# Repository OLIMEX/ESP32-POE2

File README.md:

# ESP32-POE2
Power Over Ethernet Internet of Things POE IoT board with Espressif ESP32 WiFi, Bluetooth and wired 100Mbit Ethehernet with 25W power delivery

https://www.olimex.com/Products/IoT/ESP32/ESP32-POE2/open-source-hardware

## Licensee
* Hardware is released under CERN Open Hardware Licence Version 2 - Strongly Reciprocal
* Box design is released under CC BY 4.0 License
* Software is released under GPL V3 Licensee
* Documentation is released under CC BY-SA 4.0

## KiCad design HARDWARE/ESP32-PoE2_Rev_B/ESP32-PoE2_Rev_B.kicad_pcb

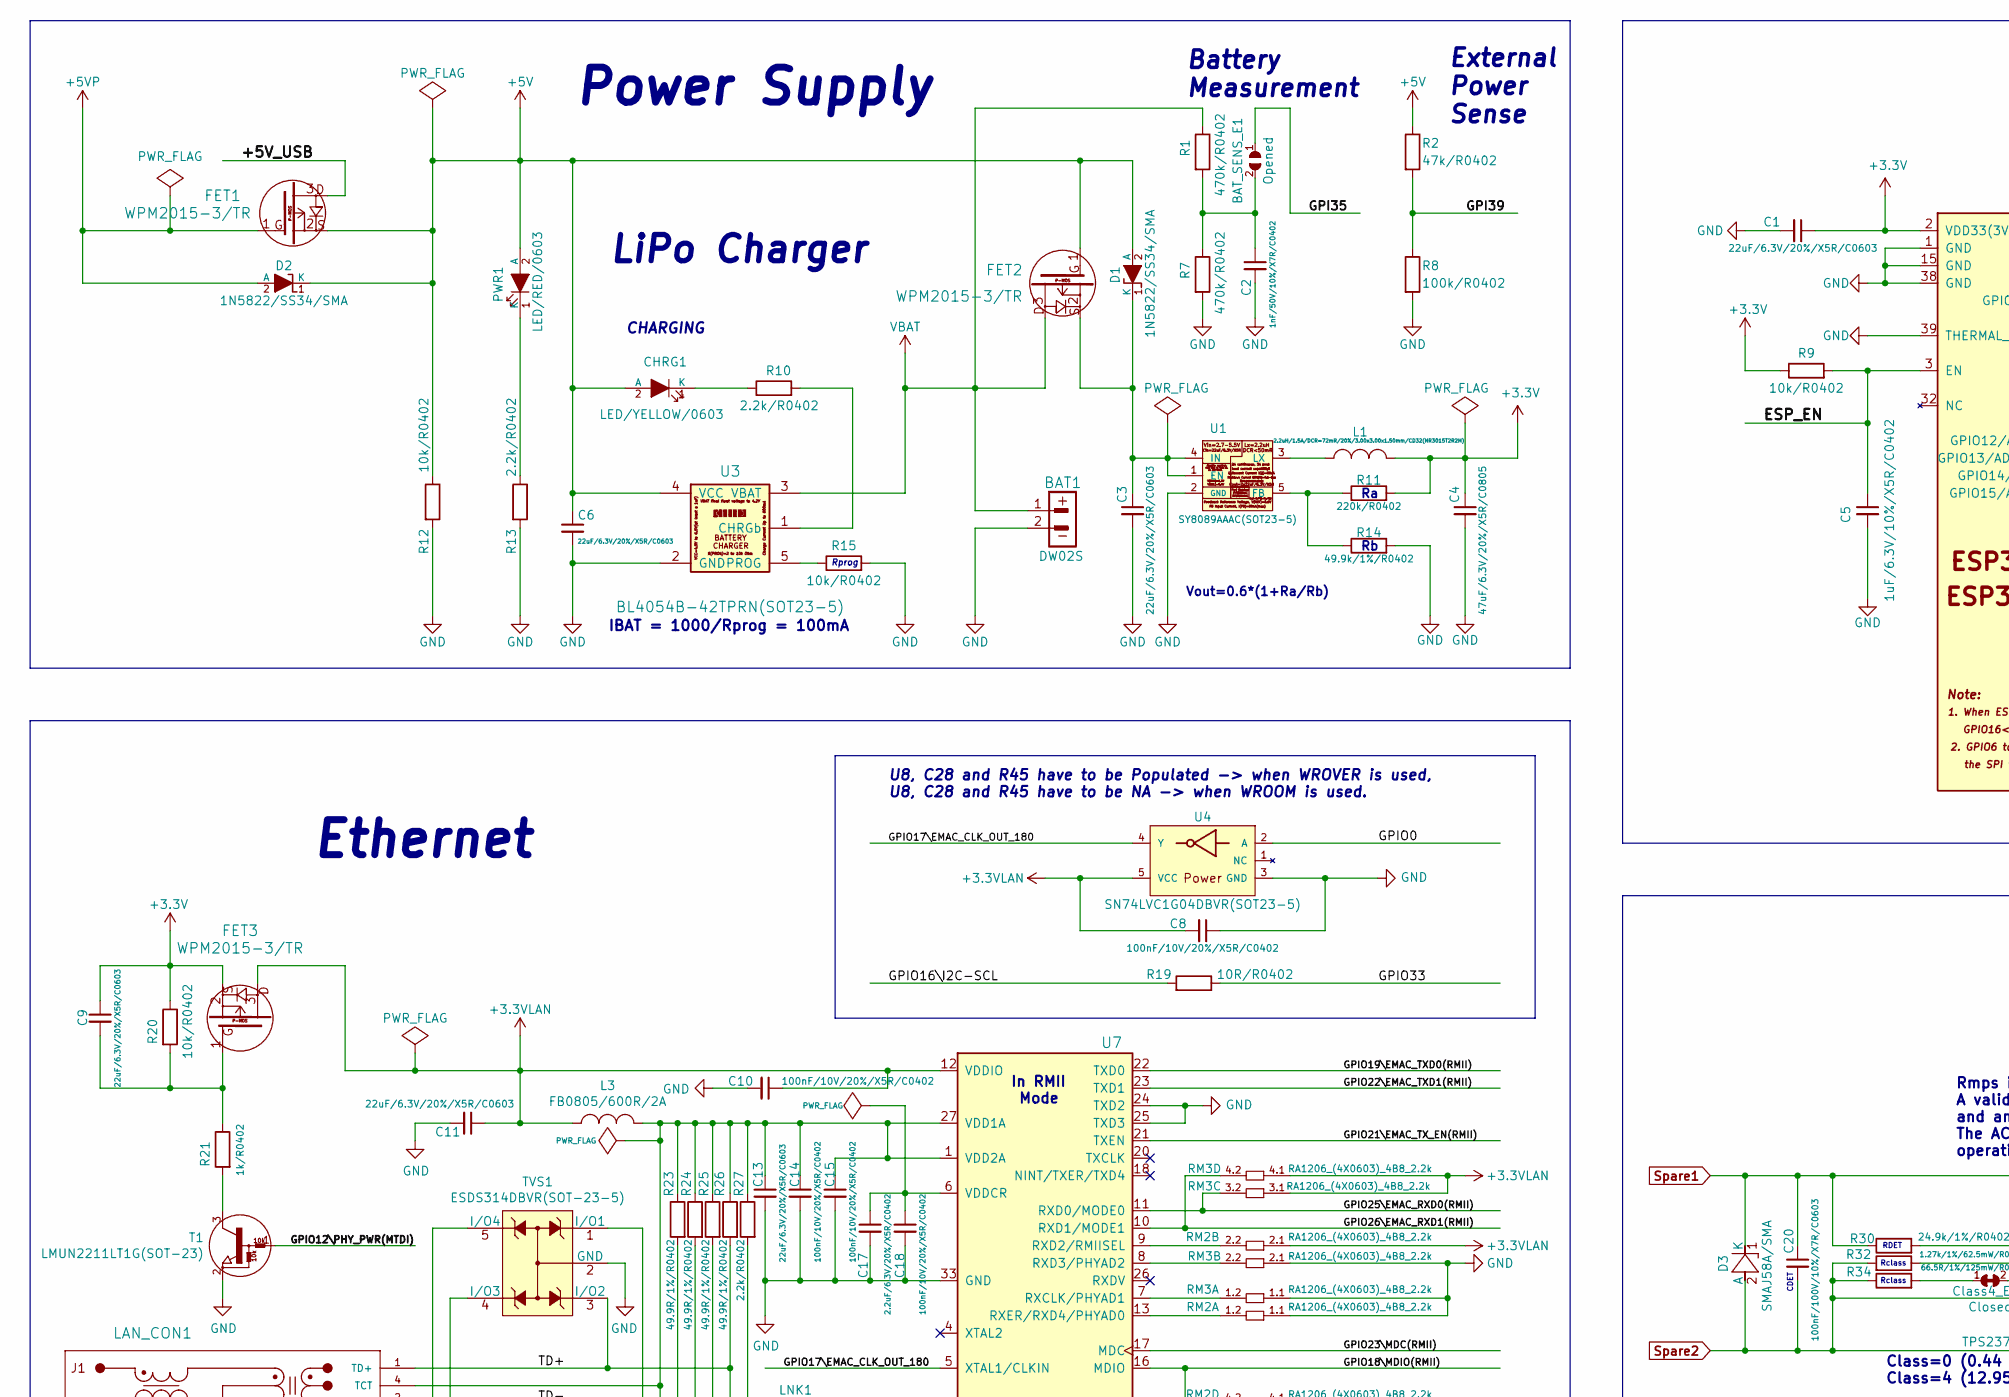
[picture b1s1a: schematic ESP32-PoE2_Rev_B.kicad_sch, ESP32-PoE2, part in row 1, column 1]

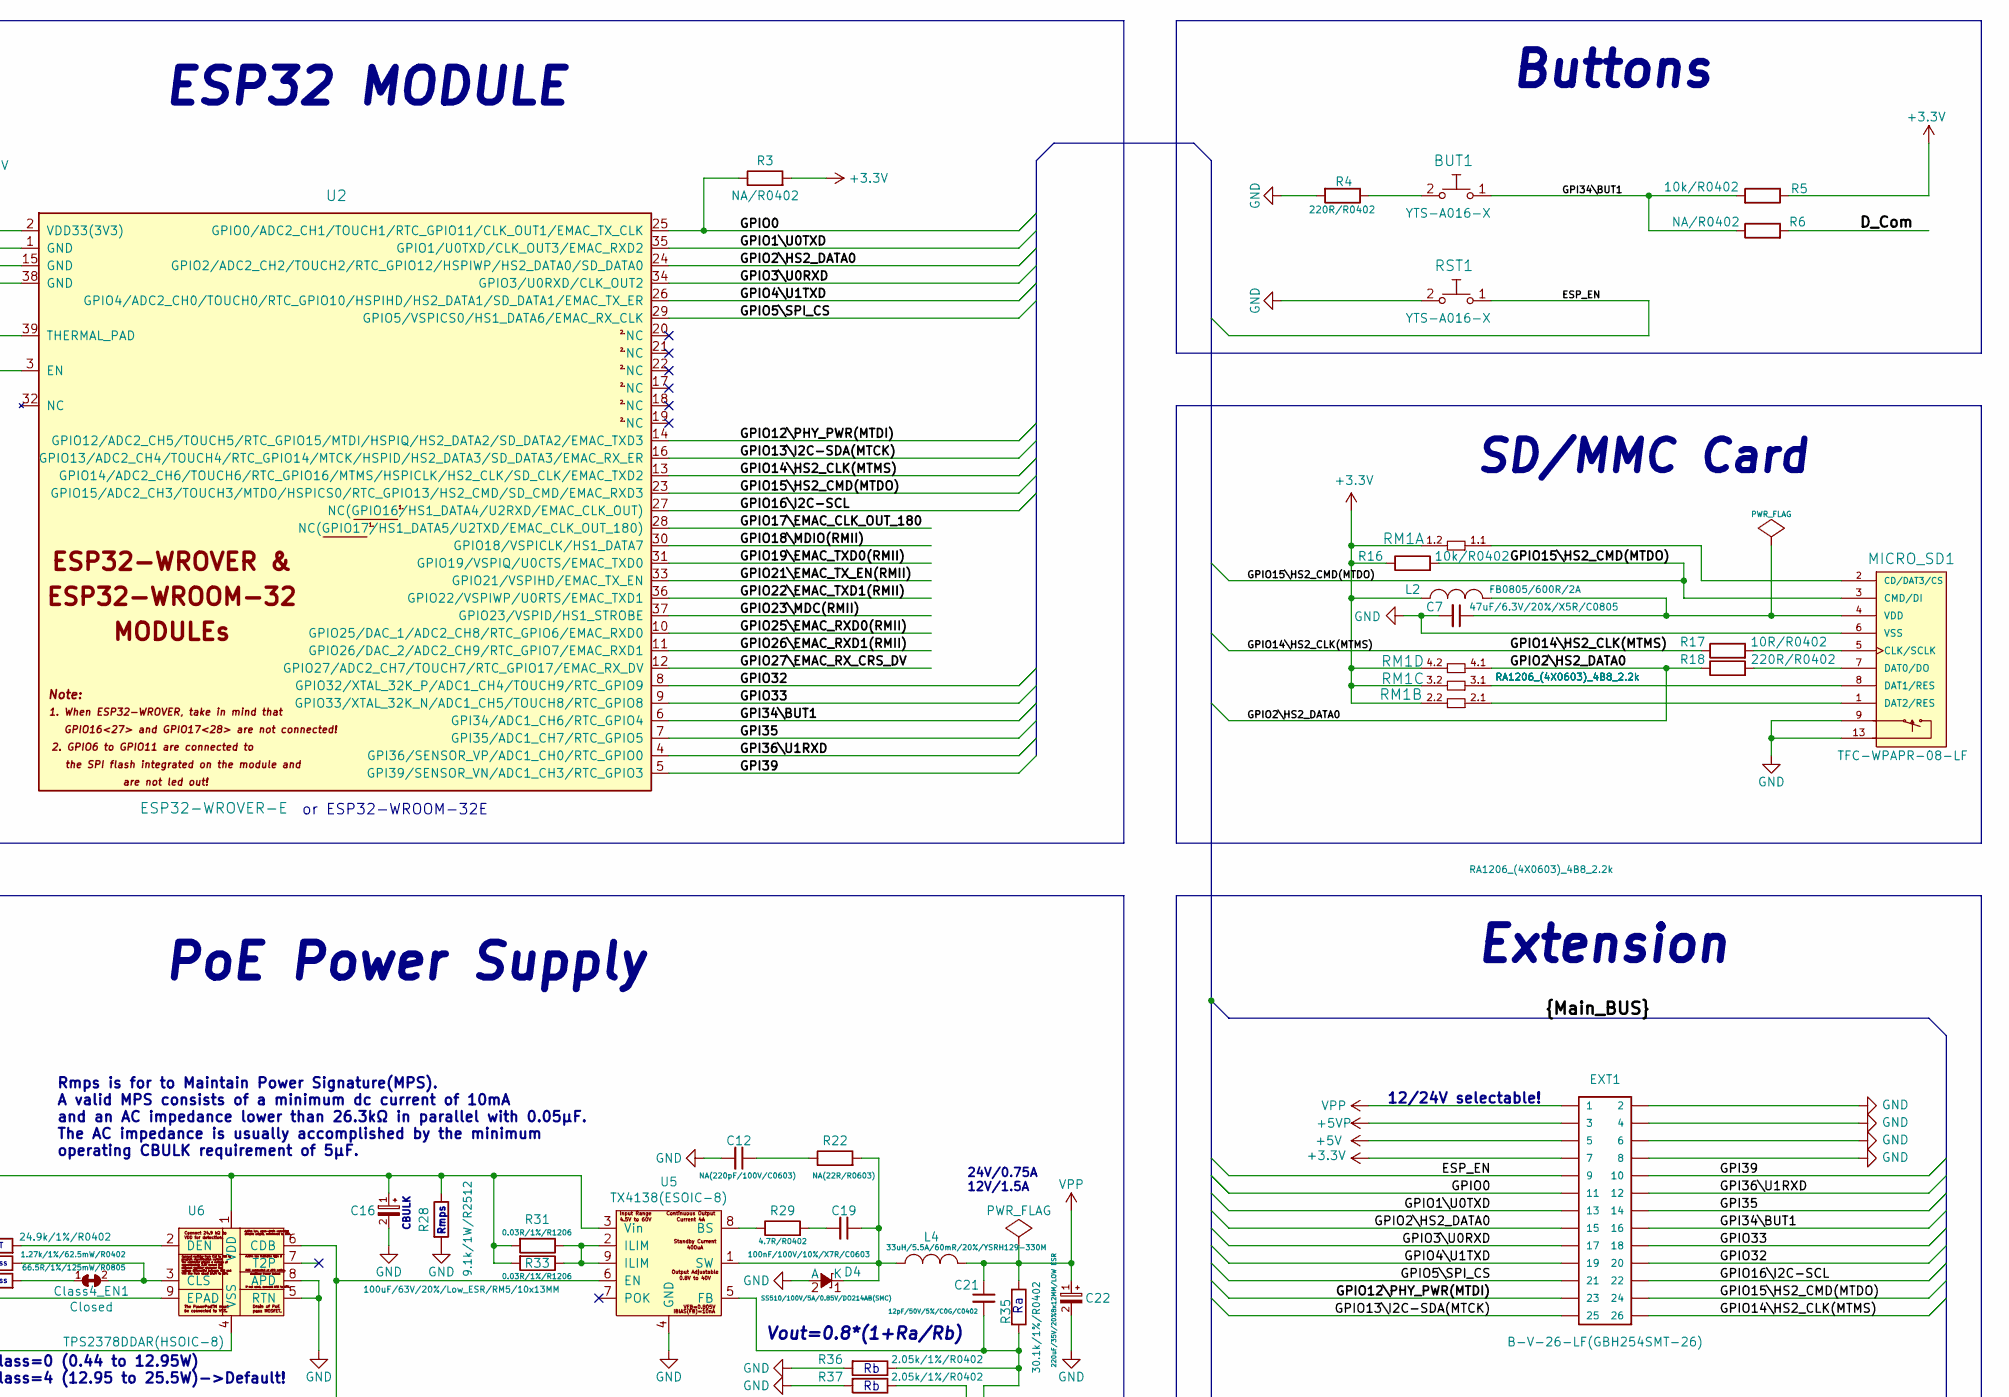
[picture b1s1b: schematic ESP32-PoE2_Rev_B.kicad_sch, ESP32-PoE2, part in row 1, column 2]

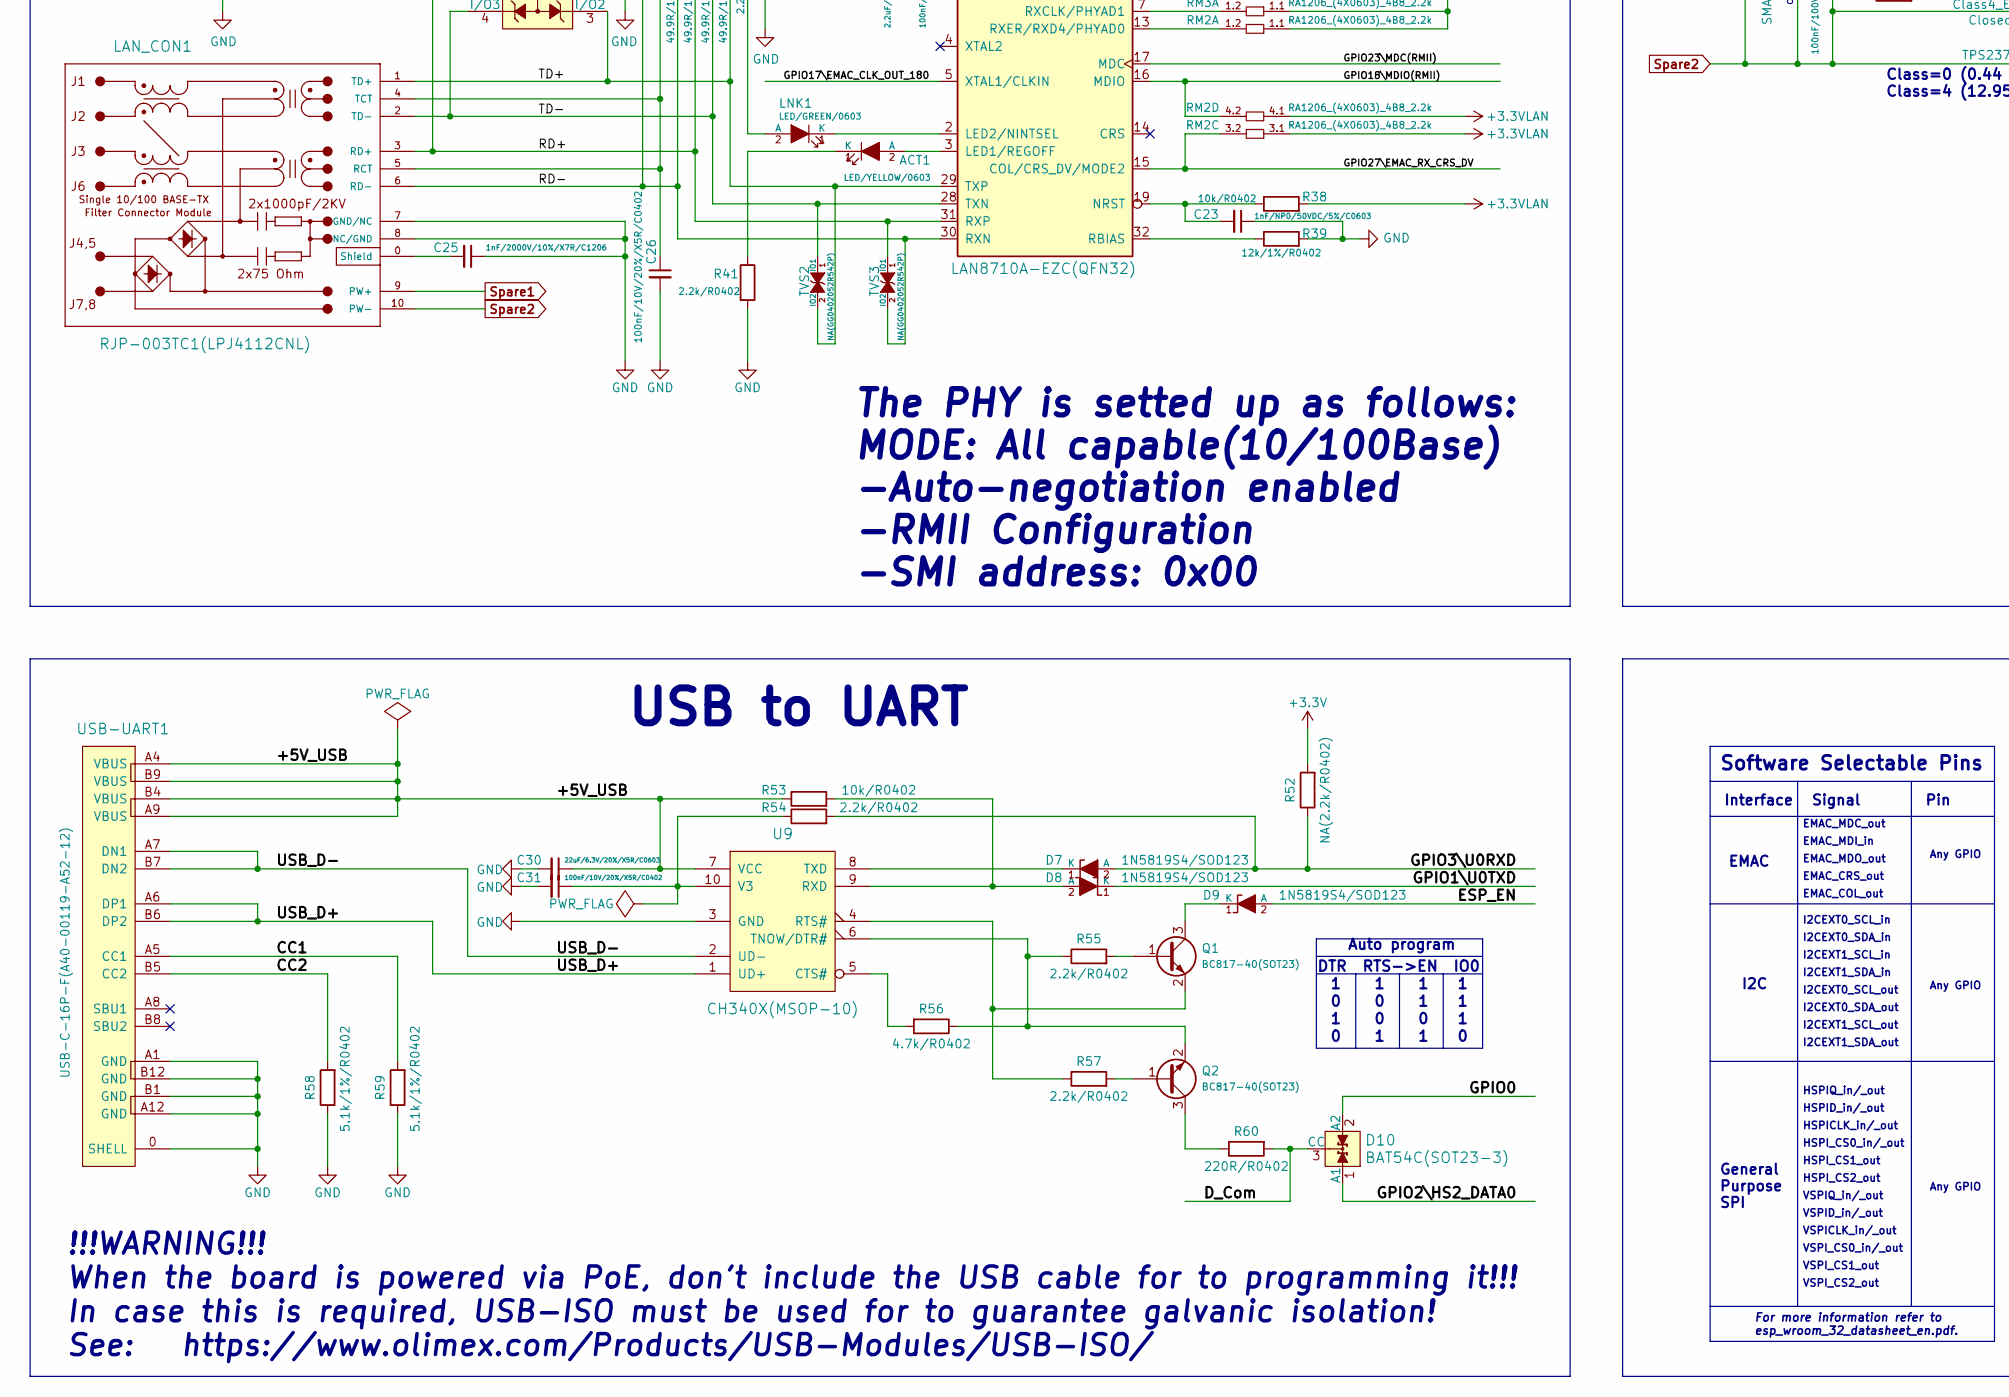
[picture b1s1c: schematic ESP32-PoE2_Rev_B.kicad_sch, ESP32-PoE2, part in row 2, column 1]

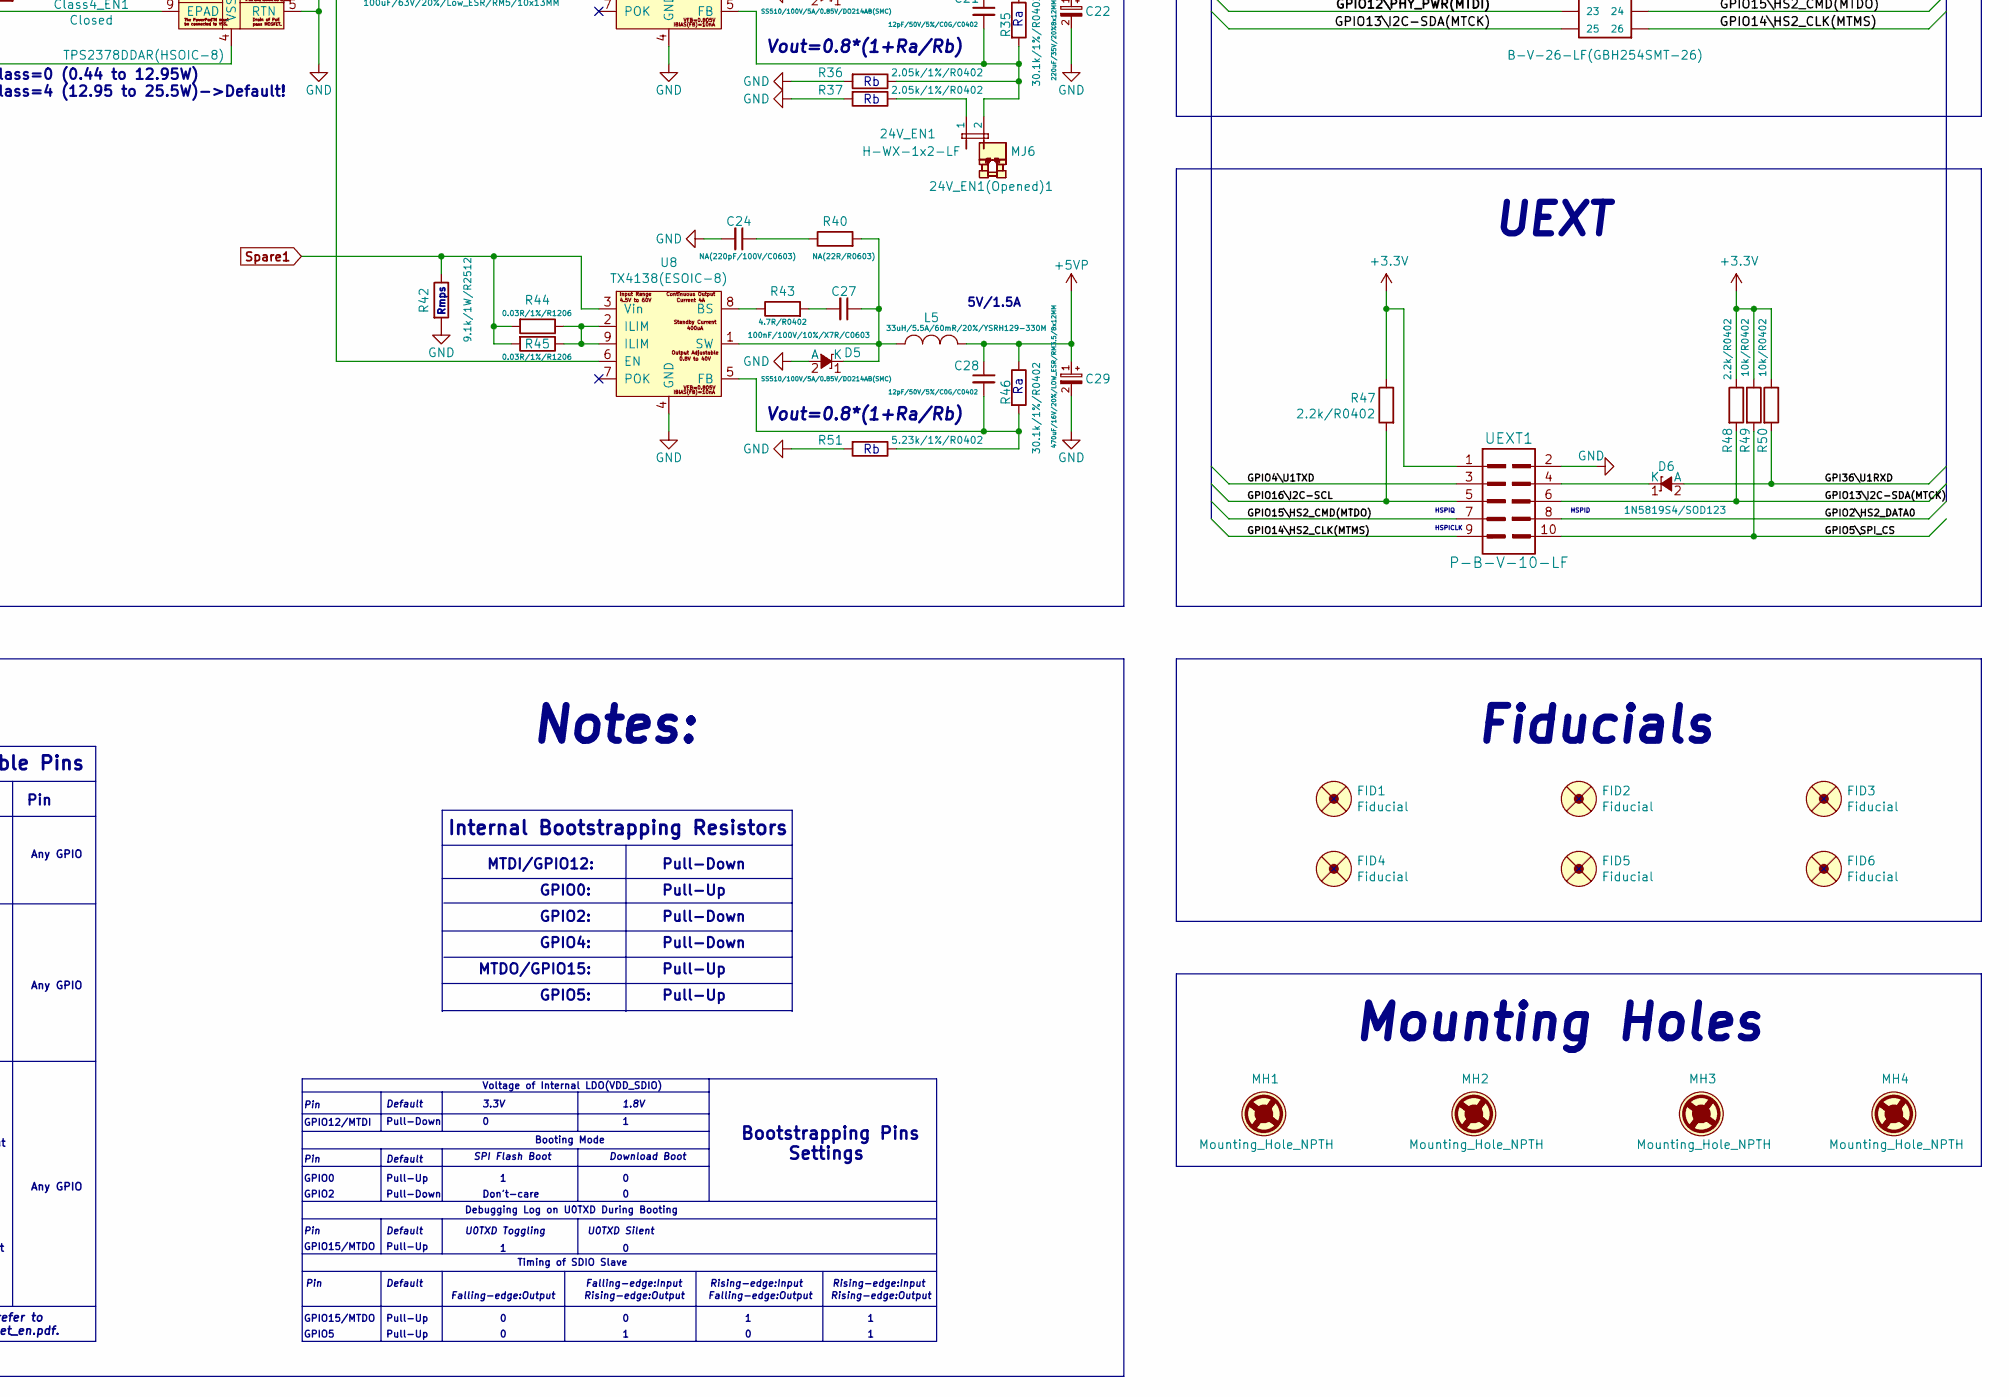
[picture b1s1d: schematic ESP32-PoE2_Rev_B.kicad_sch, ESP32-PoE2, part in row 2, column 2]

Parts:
24V_EN1: H-WX-1x2-LF; HN1x2(SMD)_H-WX-1x2-LF
24V_EN1(Opened)1: MJ6
ACT1: LED/YELLOW/0603; LED_0603_KA
BAT1: DW02S; LIPO_BAT_VERTICAL_DW02S
BAT_SENS_E1: Opened; SJ
BUT1: YTS-A016-X
C1, C3, C6, C9, C11, C13, C30: 22uF/6.3V/20%/X5R/C0603; C_0603_5MIL_DWS
C2: 1nF/50V/10%/X7R/C0402; C_0402_5MIL_DWS
C4, C7: 47uF/6.3V/20%/X5R/C0805; C_0805_5MIL_DWS
C5: 1uF/6.3V/10%/X5R/C0402; C_0402_5MIL_DWS
C8, C10, C14, C15, C18, C26, C31: 100nF/10V/20%/X5R/C0402; C_0402_5MIL_DWS
C12, C24: NA(220pF/100V/C0603); C_0603_5MIL_DWS
C16: 100uF/63V/20%/Low_ESR/RM5/10x13MM; CPOL-RM5mm_10.0x16.0mm_PTH
C17: 2.2uF/6.3V/20%/X5R/C0402; C_0402_5MIL_DWS
C19, C20, C27: 100nF/100V/10%/X7R/C0603; C_0603_5MIL_DWS
C21, C28: 12pF/50V/5%/C0G/C0402; C_0402_5MIL_DWS
C22: 220uF/35V/20%8x12MM/LOW ESR; CPOL-RM3.5mm_8.0x11.5mm_PTH
C23: 1nF/NP0/50VDC/5%/C0603; C_0603_5MIL_DWS
C25: 1nF/2000V/10%/X7R/C1206; C_1206_5MIL_DWS_ISO
C29: 470uF/16V/20%/LOW_ESR/RM3.5/8x12MM; CPOL-RM3.5mm_8.0x11.5mm_PTH
CHRG1: LED/YELLOW/0603; LED_0603_KA
Class4_EN1: Closed; SJ_Closed
D1, D2: 1N5822/SS34/SMA; SMA-KA
D3: SMAJ58A/SMA; SMA-KA
D4, D5: SS510/100V/5A/0.85V/DO214AB(SMC); DO214AB(SMC)_1(K)-2(A)
D6, D7, D8, D9: 1N5819S4/SOD123; SOD-123_1C-2A_KA
D10: BAT54C(SOT23-3); SOT23-3
EXT1: B-V-26-LF(GBH254SMT-26); GBH-254-SMT-26
FET1, FET2, FET3: WPM2015-3/TR; SOT23
FID1, FID2, FID3: Fiducial; Fiducial1x3_Paste
FID4, FID5, FID6: Fiducial; Fiducial1x3
L1: 2.2uH/1.5A/DCR=72mR/20%/3.00x3.00x1.50mm/CD32(NR3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; CD32
L2, L3: FB0805/600R/2A; L_0805_5MIL_DWS
L4, L5: 33uH/5.5A/60mR/20%/YSRH129-330M; HSMRH129_12.0x12.5x9.5(max)
LAN_CON1: RJP-003TC1(LPJ4112CNL)
LNK1: LED/GREEN/0603; LED_0603_KA
MH1, MH2, MH3, MH4: Mounting_Hole_NPTH; Mounting_Hole_Drill-3.3mm_Clerance-7mm
MICRO_SD1: TFC-WPAPR-08-LF; TFC-WPAPR-08
PWR1: LED/RED/0603; LED_0603_KA
Q1, Q2: BC817-40(SOT23); SOT23
R1, R7: 470k/R0402; R_0402_5MIL_DWS
R2: 47k/R0402; R_0402_5MIL_DWS
R3, R6: NA/R0402; R_0402_5MIL_DWS
R4, R18, R60: 220R/R0402; R_0402_5MIL_DWS
R5, R9, R12, R15, R16, R20, R38, R49, R50, R53: 10k/R0402; R_0402_5MIL_DWS
R8: 100k/R0402; R_0402_5MIL_DWS
R10, R13, R27, R41, R47, R48, R54, R55, R57: 2.2k/R0402; R_0402_5MIL_DWS
R11: 220k/R0402; R_0402_5MIL_DWS
R14: 49.9k/1%/R0402; R_0402_5MIL_DWS
R17, R19: 10R/R0402; R_0402_5MIL_DWS
R21: 1k/R0402; R_0402_5MIL_DWS
R22, R40: NA(22R/R0603); R_0603_5MIL_DWS
R23, R24, R25, R26: 49.9R/1%/R0402; R_0402_5MIL_DWS
R28, R42: 9.1k/1W/R2512; R_2512_MM_DWS
R29, R43: 4.7R/R0402; R_0402_5MIL_DWS
R30: 24.9k/1%/R0402; R_0402_5MIL_DWS
R31, R33, R44, R45: 0.03R/1%/R1206; R_1206_5MIL_DWS
R32: 1.27k/1%/62.5mW/R0402; R_0402_5MIL_DWS
R34: 66.5R/1%/125mW/R0805; R_0805_5MIL_DWS
R35, R46: 30.1k/1%/R0402; R_0402_5MIL_DWS
R36, R37: 2.05k/1%/R0402; R_0402_5MIL_DWS
R39: 12k/1%/R0402; R_0402_5MIL_DWS
R51: 5.23k/1%/R0402; R_0402_5MIL_DWS
R52: NA(2.2k/R0402); R_0402_5MIL_DWS
R56: 4.7k/R0402; R_0402_5MIL_DWS
R58, R59: 5.1k/1%/R0402; R_0402_5MIL_DWS
RM1, RM2, RM3: RA1206_(4X0603)_4B8_2.2k; R_MATRIX_4
RST1: YTS-A016-X
T1: LMUN2211LT1G(SOT-23); SOT23
TVS1: ESDS314DBVR(SOT-23-5); SOT-23-5
TVS2, TVS3: NA(GG0402052R542P); D_0402_5MIL_DWS
U1: SY8089AAAC(SOT23-5); SOT-23-5
U2: ESP32-WROVER-E; ESP32-WROVER(WROOM)-UNIVERSAL_MODULE
U3: BL4054B-42TPRN(SOT23-5); SOT-23-5
U4: SN74LVC1G04DBVR(SOT23-5); SOT-23-5
U5, U8: TX4138(ESOIC-8); ESOIC-8
U6: TPS2378DDAR(HSOIC-8); ESOIC-8
U7: LAN8710A-EZC(QFN32); QFN32_EP(33)_5.00x5.00x0.90mm_Pitch_0.50mm
U9: CH340X(MSOP-10); MSOP-10_Pitch-0.5mm_3.00x3.00x1.00mm
UEXT1: P-B-V-10-LF; GBH-254-SMT-10
USB-UART1: USB-C-16P-F(A40-00119-A52-12); USB2.0_TYPE-C(A40-00119-A52-12)_Paste

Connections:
+3.3V: C1.1, C4.1, C9.1, EXT1.7, FET3.2, L1.2, L2.1, R3.2, R5.1, R9.1, R11.2, R16.1, R20.1, R47.1, R48.1, R49.1, R50.1, R52.2, RM1.1.2, RM1.2.2, RM1.3.2, RM1.4.2, U2.2 (VDD33(3V3)), UEXT1.1
+3.3VLAN: C8.2, C10.1, C11.1, FET3.3, L3.1, R38.2, RM2.2.1, RM2.3.1, RM2.4.1, RM3.3.1, RM3.4.1, U4.5 (VCC), U7.12 (VDDIO)
+5V: C6.1, CHRG1.2 (A), D1.2 (A), D2.1 (K), EXT1.5, FET1.2, FET2.1, PWR1.2 (A), R2.1, R12.1, U3.4 (VCC)
+5VP: C28.1, C29.1 (+), D2.2 (A), EXT1.3, FET1.1, L5.2, R46.1
/+5V_USB: C30.1, FET1.3, R53.1, U9.7 (VCC), USB-UART1.A4 (VBUS), USB-UART1.A9 (VBUS), USB-UART1.B4 (VBUS), USB-UART1.B9 (VBUS)
/CC1: R59.2, USB-UART1.A5 (CC1)
/CC2: R58.2, USB-UART1.B5 (CC2)
/D_Com: D10.3 (CC), R6.2, R60.2
/ESP_EN: C5.1, D9.2 (A), EXT1.9, R9.2, RST1.1, U2.3 (EN)
/GPI34\BUT1: BUT1.1, EXT1.16, R5.2, R6.1, U2.6 (GPI34/ADC1_CH6/RTC_GPIO4)
/GPI35: BAT_SENS_E1.1, EXT1.14, U2.7 (GPI35/ADC1_CH7/RTC_GPIO5)
/GPI36\U1RXD: D6.2 (A), EXT1.12, R50.2, U2.4 (GPI36/SENSOR_VP/ADC1_CH0/RTC_GPIO0)
/GPI39: EXT1.10, R2.2, R8.1, U2.5 (GPI39/SENSOR_VN/ADC1_CH3/RTC_GPIO3)
/GPIO0: D10.2 (A2), EXT1.11, R3.1, U2.25 (GPIO0/ADC2_CH1/TOUCH1/RTC_GPIO11/CLK_OU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), U4.2 (A)
/GPIO1\U0TXD: D8.1 (K), EXT1.13, U2.35 (GPIO1/U0TXD/CLK_OUT3/EMAC_RXD2)
/GPIO2\HS2_DATA0: D10.1 (A1), EXT1.15, R18.1, RM1.4.1, U2.24 (GPIO2/ADC2_CH2/TOUCH2/RTC_GPIO12/HSPIWP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), UEXT1.8
/GPIO3\U0RXD: D7.2 (A), EXT1.17, R52.1, R54.2, U2.34 (GPIO3/U0RXD/CLK_OUT2)
/GPIO4\U1TXD: EXT1.19, U2.26 (GPIO4/ADC2_CH0/TOUCH0/RTC_GPIO10/HSPIHD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), UEXT1.3
/GPIO5\SPI_CS: EXT1.21, R49.2, U2.29 (GPIO5/VSPICS0/HS1_DATA6/EMAC_RX_CLK), UEXT1.10
/GPIO12\PHY_PWR(MTDI): EXT1.23, T1.1 (B), U2.14 (GPIO12/ADC2_CH5/TOUCH5/RTC_GPIO15/MTDI/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)
/GPIO13\I2C-SDA(MTCK): EXT1.25, R48.2, U2.16 (GPIO13/ADC2_CH4/TOUCH4/RTC_GPIO14/MTCK/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), UEXT1.6
/GPIO14\HS2_CLK(MTMS): EXT1.26, R17.1, U2.13 (GPIO14/ADC2_CH6/TOUCH6/RTC_GPIO16/MTMS/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), UEXT1.9
/GPIO15\HS2_CMD(MTDO): EXT1.24, MICRO_SD1.3 (CMD/DI), R16.2, U2.23 (GPIO15/ADC2_CH3/TOUCH3/MTDO/HSPICS0/RTC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), UEXT1.7
/GPIO16\I2C-SCL: EXT1.22, R19.2, R47.2, U2.27 (NC(GPIO16/HS1_DATA4/U2RXD/EMAC_CLK_OUT)), UEXT1.5
/GPIO17\EMAC_CLK_OUT_180: U2.28 (NC(GPIO17/HS1_DATA5/U2TXD/EMAC_CLK_OUT_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), U4.4 (Y), U7.5 (XTAL1/CLKIN)
/GPIO18\MDIO(RMII): RM2.4.2, U2.30 (GPIO18/VSPICLK/HS1_DATA7), U7.16 (MDIO)
/GPIO19\EMAC_TXD0(RMII): U2.31 (GPIO19/VSPIQ/U0CTS/EMAC_TXD0), U7.22 (TXD0)
/GPIO21\EMAC_TX_EN(RMII): U2.33 (GPIO21/VSPIHD/EMAC_TX_EN), U7.21 (TXEN)
/GPIO22\EMAC_TXD1(RMII): U2.36 (GPIO22/VSPIWP/U0RTS/EMAC_TXD1), U7.23 (TXD1)
/GPIO23\MDC(RMII): U2.37 (GPIO23/VSPID/HS1_STROBE), U7.17 (MDC)
/GPIO25\EMAC_RXD0(RMII): RM3.3.2, U2.10 (GPIO25/DAC_1/ADC2_CH8/RTC_GPIO6/EMAC_RX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), U7.11 (RXD0/MODE0)
/GPIO26\EMAC_RXD1(RMII): RM3.4.2, U2.11 (GPIO26/DAC_2/ADC2_CH9/RTC_GPIO7/EMAC_RX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), U7.10 (RXD1/MODE1)
/GPIO27\EMAC_RX_CRS_DV: RM2.3.2, U2.12 (GPIO27/ADC2_CH7/TOUCH7/RTC_GPIO17/EMAC_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), U7.15 (COL/CRS_DV/MODE2)
/GPIO32: EXT1.20, U2.8 (GPIO32/XTAL_32K_P/ADC1_CH4/TOUCH9/RTC_G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)
/GPIO33: EXT1.18, R19.1, U2.9 (GPIO33/XTAL_32K_N/ADC1_CH5/TOUCH8/RTC_G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)
/RD+: LAN_CON1.3 (RD+), R24.2, TVS1.5 (I/O4), TVS3.1 (IO1), U7.31 (RXP)
/RD-: LAN_CON1.6 (RD-), R23.2, TVS1.1 (I/O1), TVS3.2 (IO2), U7.30 (RXN)
/TD+: LAN_CON1.1 (TD+), R26.2, TVS1.3 (I/O2), TVS2.2 (IO2), U7.29 (TXP)
/TD-: LAN_CON1.2 (TD-), R25.2, TVS1.4 (I/O3), TVS2.1 (IO1), U7.28 (TXN)
/USB_D+: U9.1 (UD+), USB-UART1.A6 (DP1), USB-UART1.B6 (DP2)
/USB_D-: U9.2 (UD-), USB-UART1.A7 (DN1), USB-UART1.B7 (DN2)
GND: BAT1.2, C1.2, C2.2, C3.2, C4.2, C5.2, C6.2, C7.2, C8.1, C10.2, C11.2, C12.2, C13.2, C14.2, C15.2, C16.2 (-), C17.2, C18.2, C22.2 (-), C23.1, C24.2, C25.1, C26.2, C29.2 (-), C30.2, C31.2, D4.2 (A), D5.2 (A), EXT1.2, EXT1.4, EXT1.6, EXT1.8, LAN_CON1.7 (GND/NC), LAN_CON1.8 (NC/GND), MICRO_SD1.6 (VSS), MICRO_SD1.9, MICRO_SD1.10, MICRO_SD1.11, MICRO_SD1.12, MICRO_SD1.13, R4.2, R7.2, R8.2, R12.2, R13.2, R14.2, R15.2, R28.2, R36.2, R37.2, R39.2, R41.2, R42.2, R51.2, R58.1, R59.1, RM2.1.1, RM3.1.1, RM3.2.1, RST1.2, T1.2 (E), TVS1.2 (GND), U1.2 (GND), U2.1 (GND), U2.15 (GND), U2.38 (GND), U2.39 (THERMAL_PAD), U3.2 (GND), U4.3 (GND), U5.4 (GND), U6.5 (RTN), U6.8 (APD), U7.24 (TXD2), U7.25 (TXD3), U7.33 (GND), U8.4 (GND), U9.3 (GND), UEXT1.2, USB-UART1.0 (SHELL), USB-UART1.A1 (GND), USB-UART1.A12 (GND), USB-UART1.B1 (GND), USB-UART1.B12 (GND)
unnamed: 24V_EN1.1, R37.1
unnamed: ACT1.2 (A), U7.3 (LED1/REGOFF)
unnamed: ACT1.1 (K), R41.1
unnamed: BAT_SENS_E1.2, C2.1, R1.2, R7.1
unnamed: BUT1.2, R4.1
unnamed: C9.2, FET3.1, R20.2, R21.1
unnamed: C12.1, R22.1
unnamed: C19.2, R29.2
unnamed: C24.1, R40.1
unnamed: C27.2, R43.2
unnamed: CHRG1.1 (K), R10.1
unnamed: Class4_EN1.1, R34.2
unnamed: C3.1, D1.1 (K), FET2.2, U1.1 (EN), U1.4 (IN)
unnamed: C19.1, D4.1 (K), L4.1, R22.2, U5.1 (SW)
unnamed: C27.1, D5.1 (K), L5.1, R40.2, U8.1 (SW)
unnamed: D6.1 (K), UEXT1.4
unnamed: D7.1 (K), U9.8 (TXD)
unnamed: D8.2 (A), R53.2, U9.9 (RXD)
unnamed: D9.1 (K), Q1.3 (C)
unnamed: C13.1, C14.1, C15.1, C26.1, L3.2, LAN_CON1.4 (TCT), LAN_CON1.5 (RCT), R23.1, R24.1, R25.1, R26.1, R27.1, U7.1 (VDD2A), U7.27 (VDD1A)
unnamed: C25.2, LAN_CON1.0 (Shield)
unnamed: LNK1.2 (A), R27.2
unnamed: LNK1.1 (K), U7.2 (LED2/NINTSEL)
unnamed: MICRO_SD1.2 (CD/DAT3/CS), RM1.1.1
unnamed: MICRO_SD1.5 (CLK/SCLK), R17.2
unnamed: MICRO_SD1.7 (DAT0/DO), R18.2
unnamed: MICRO_SD1.8 (DAT1/RES), RM1.3.1
unnamed: MICRO_SD1.1 (DAT2/RES), RM1.2.1
unnamed: C7.1, L2.2, MICRO_SD1.4 (VDD)
unnamed: PWR1.1 (K), R13.1
unnamed: Q1.1 (B), R55.2
unnamed: Q1.2 (E), R57.1, U9.4 (RTS#)
unnamed: Q2.1 (B), R57.2
unnamed: Q2.3 (C), R60.1
unnamed: Q2.2 (E), R55.1, R56.1, U9.6 (TNOW/DTR#)
unnamed: R31.1, R33.1, U5.2 (ILIM), U5.9 (ILIM)
unnamed: R44.1, R45.1, U8.2 (ILIM), U8.9 (ILIM)
unnamed: R21.2, T1.3 (C)
unnamed: R11.1, R14.1, U1.5 (FB)
unnamed: L1.1, U1.3 (LX)
unnamed: R10.2, U3.1 (CHRGb)
unnamed: R15.1, U3.5 (PROG)
unnamed: R29.1, U5.8 (BS)
unnamed: U5.6 (EN), U6.6 (CDB), U8.6 (EN)
unnamed: 24V_EN1.2, C21.2, R35.2, R36.1, U5.5 (FB)
unnamed: Class4_EN1.2, R32.1, U6.3 (CLS)
unnamed: R30.2, U6.2 (DEN)
unnamed: C23.2, R38.1, U7.19 (NRST)
unnamed: R39.1, U7.32 (RBIAS)
unnamed: RM3.1.2, U7.7 (RXCLK/PHYAD1)
unnamed: RM2.2.2, U7.9 (RXD2/RMIISEL)
unnamed: RM3.2.2, U7.8 (RXD3/PHYAD2)
unnamed: RM2.1.2, U7.13 (RXER/RXD4/PHYAD0)
unnamed: C17.1, C18.1, U7.6 (VDDCR)
unnamed: R43.1, U8.8 (BS)
unnamed: C28.2, R46.2, R51.1, U8.5 (FB)
unnamed: R56.2, U9.5 (CTS#)
unnamed: C31.1, R54.1, U9.10 (V3)
Spare1: C16.1 (+), C20.1, D3.1 (K), LAN_CON1.9 (PW+), R28.1, R30.1, R31.2, R33.2, R42.1, R44.2, R45.2, U5.3 (Vin), U6.1 (VDD), U8.3 (Vin)
Spare2: C20.2, D3.2 (A), LAN_CON1.10 (PW-), R32.2, R34.1, U6.4 (VSS), U6.9 (EPAD)
VBAT: BAT1.1, FET2.3, R1.1, U3.3 (VBAT)
VPP: C21.1, C22.1 (+), EXT1.1, L4.2, R35.1

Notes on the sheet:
VSPI_CS0_in/_out
U0TXD Silent
CHARGING
Software Selectable Pins
Buttons
Voltage of Internal LDO(VDD_SDIO)
GPIO4:
Pull-Down
3.3V
EMAC_CRS_out
Pull-Up
GPIO0:
Vout=0.8*(1+Ra/Rb)
VSPID_in/_out
24V/0.75A 12V/1.5A
Download Boot
SD/MMC Card
Rmps
Default
EMAC_COL_out
Signal
Rising-edge:Input
I2CEXT0_SDA_in
Internal Bootstrapping Resistors
Auto program
EMAC_MDI_in
Extension
RDET
Class=0 (0.44 to 12.95W) Class=4 (12.95 to 25.5W)->Default!
Any GPIO
Rising-edge:Output
IBAT = 1000/Rprog = 100mA
Rclass
General Purpose SPI
Power Supply
HSPI_CS1_out
HSPID
UEXT
Pin
GPIO2:

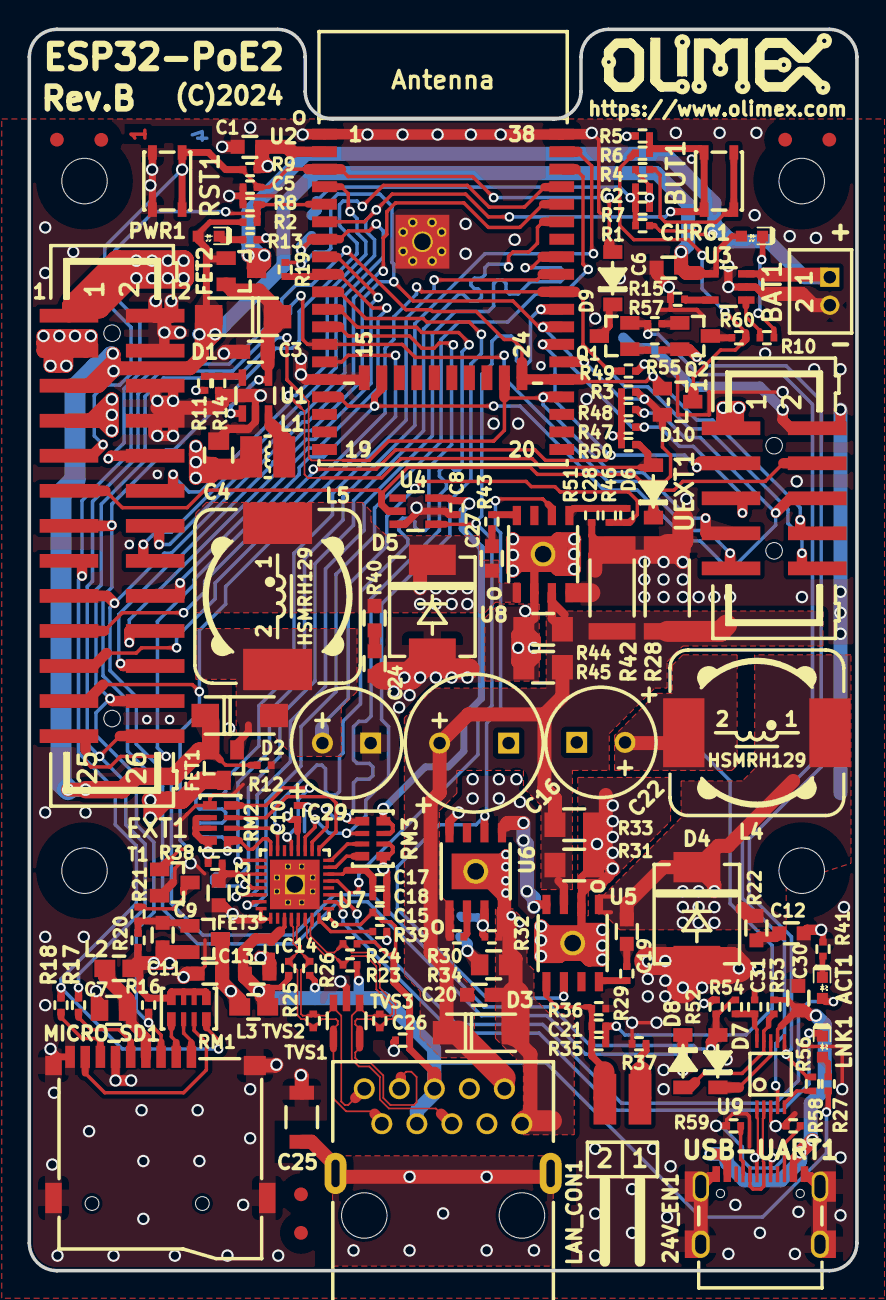
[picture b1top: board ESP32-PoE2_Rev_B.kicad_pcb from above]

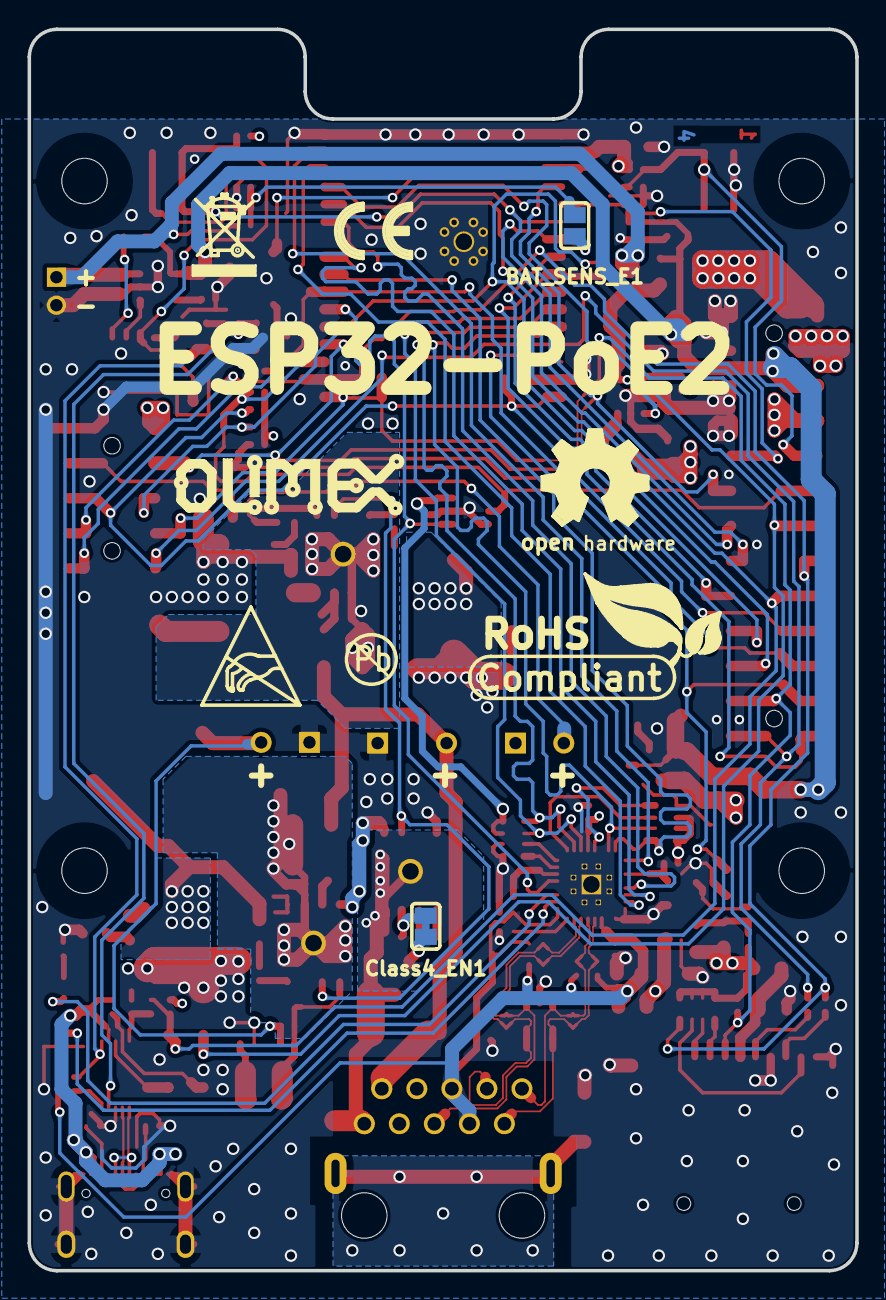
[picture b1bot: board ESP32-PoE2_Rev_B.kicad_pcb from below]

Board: 4 copper layers, 60.0 x 90.0 mm, 161 parts (9 on the bottom side), 104 nets.

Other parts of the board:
CE: CE_Sign
Logo_OLIMEX_TB: Logo_OLIMEX_TB
Logo_Olimex: OLIMEX_LOGO_TB
Sign_Antistatic: Sign_Antistatic
Sign_OSHW_8x8: Sign_OSHW_8x8
Sign_PB-Free: Sign_PB-Free
Sign_RecycleBin_1: Sign_RecycleBin_1
Sign_RoHS_1: Sign_RoHS_1

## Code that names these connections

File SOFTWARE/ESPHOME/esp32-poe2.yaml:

esphome:
  name: esp32-poe2
  comment: Olimex ESP32-POE2 (WROVER-E N4R8) with UEXT support

esp32:
  board: esp32dev
  framework:
    type: arduino

psram:
  mode: quad
  speed: 80MHz

logger:

# ================= NETWORKING =================

# ---- WiFi (Primary) ----
# remember to add credentials in a secret file
wifi:
  ssid: !secret wifi_ssid
  password: !secret wifi_password
  ap:
    ssid: "ESP32-POE2 Fallback"
    password: "fallback123"

captive_portal:

# ---- Ethernet (Secondary / Backup) ----
# You can't use WIFI and Ethernet simultaneously
# in ESPHOME, if you wish to use Ethernet:
# uncomment Ethernet section below, and
# comment the WIFI section above

#ethernet:
#  type: LAN8720
#  mdc_pin: GPIO23
#  mdio_pin: GPIO18
#  clk:
#    pin: GPIO0
#    mode: CLK_OUT
#  phy_addr: 0
#  power_pin: GPIO12

# ================= ONBOARD IO =================

# ---- User Button (BUT1) ----
binary_sensor:
  - platform: gpio
    name: "BUT1 Button"
    pin:
      number: GPIO34
      mode: INPUT

# ---- External Power Sense ----
sensor:
  - platform: adc
    pin: GPIO39
    name: "External Power Sense"
    attenuation: 12db
    update_interval: 10s

# ================= UEXT CONNECTOR =================

# ---- UART1 on UEXT ----
uart:
  - id: uext_uart
    tx_pin: GPIO4
    rx_pin: GPIO36
    baud_rate: 115200

# ---- I2C Bus on UEXT ----
i2c:
  - id: uext_i2c
    scl: GPIO33
    sda: GPIO13
    scan: true

# ---- SPI Bus on UEXT (shared with SD card pins) ----
# NOTE: Cannot be used together with SD card
spi:
  - id: uext_spi
    clk_pin: GPIO14
    mosi_pin: GPIO2
    miso_pin: GPIO15

# ================= OPTIONAL SD CARD (DISABLED) =================
# Uses same pins as UEXT SPI
# To enable SD, REMOVE the SPI section above first.
#
# spi:
#   clk_pin: GPIO14
#   mosi_pin: GPIO15
#   miso_pin: GPIO2

# ================= CORE SERVICES =================
ota:
  - platform: esphome

api:

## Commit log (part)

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2024-04-25 initial upload
2024-05-15 Update
    Added dimensions
2024-05-16 Delete
2025-08-21 New demo
    Demo for MOD-ENV and ESP32-POE2
2025-09-03 Update
    Added FAQ to the datasheet
2025-10-16 New demo
    ESP32-POE2 + MOD-RTC
2025-10-16 Update
    New version of the users manual
2025-10-24 Update
    Update on the manual and improvement over the UEXT pinout for this board
2025-11-03 New Arduino demo
    PSRAM test
2026-01-07 adding files for 3d printed case
2026-02-10 Update
    Added configs for platformio and esphome
2026-03-27 Update esp32-poe2.yaml
    Updated to be compliant with latest esphome versions
2026-03-27 Update esp32-poe2.yaml
    spelling

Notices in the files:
HARDWARE/ESP32-PoE2_Rev_B/ESP32-PoE2_Rev_B.kicad_pcb:
(C)2024
